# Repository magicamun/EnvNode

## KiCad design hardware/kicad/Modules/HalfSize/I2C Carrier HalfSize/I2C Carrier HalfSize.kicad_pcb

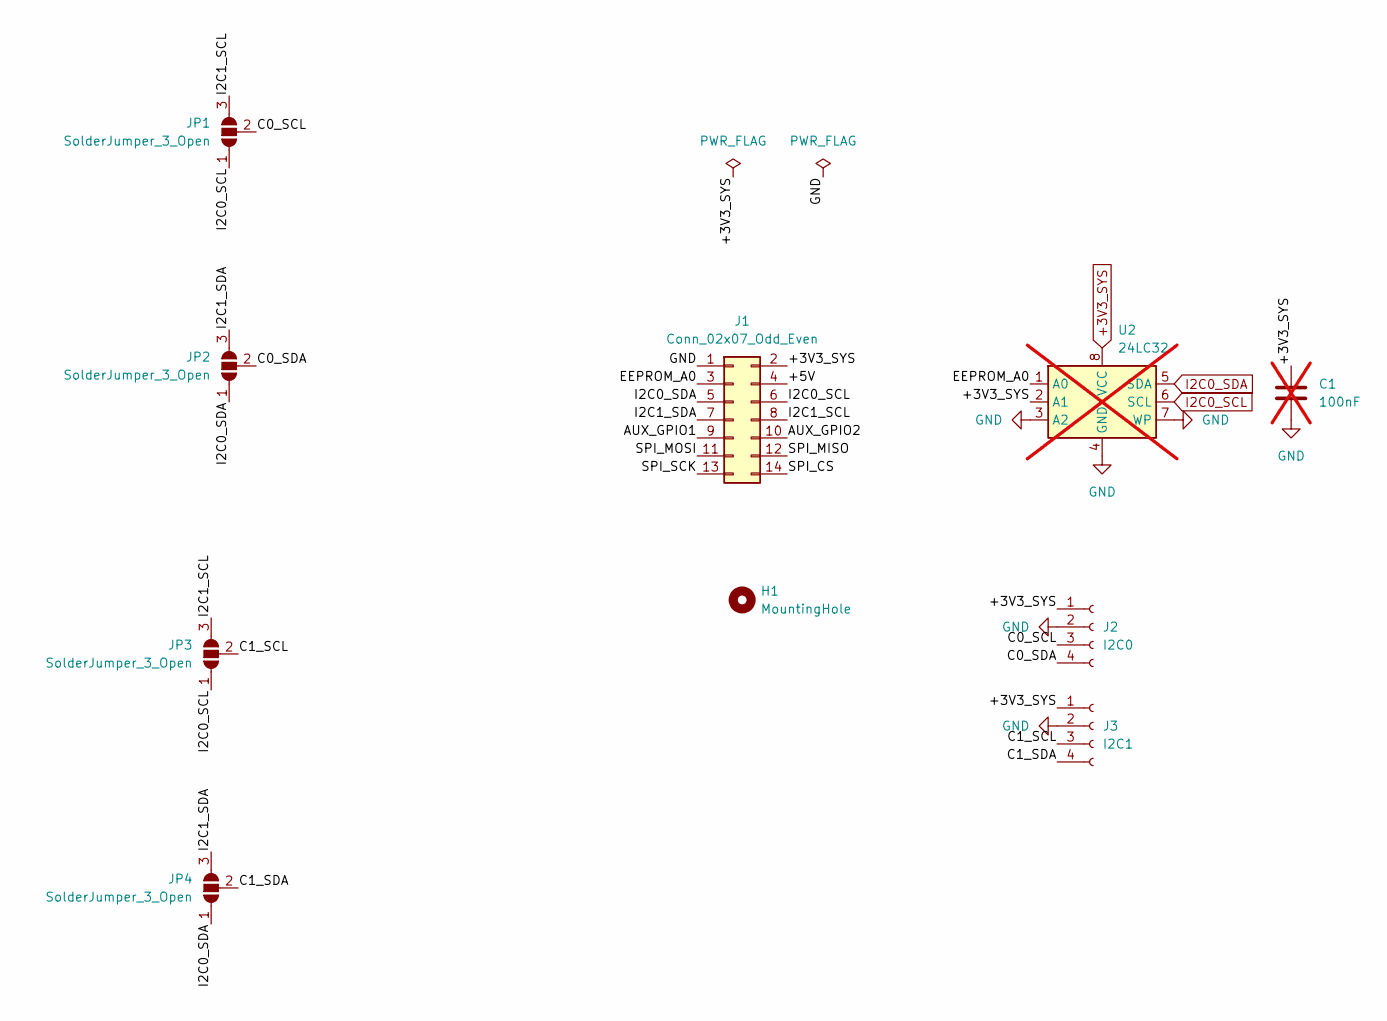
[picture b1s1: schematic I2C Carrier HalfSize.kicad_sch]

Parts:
C1: 100nF; C_1206_3216Metric_Pad1.33x1.80mm_HandSolder; not fitted
H1: MountingHole; MountingHole_2.7mm_M2.5_DIN965
J1: Conn_02x07_Odd_Even; PinHeader_2x07_P2.54mm_Vertical_Bottom
J2: I2C0; PinSocket_1x04_P2.54mm_Vertical
J3: I2C1; PinSocket_1x04_P2.54mm_Vertical
JP1, JP2, JP3, JP4: SolderJumper_3_Open; SolderJumper-3_P1.3mm_Open_RoundedPad1.0x1.5mm
U2: 24LC32; SOIC-8_3.9x4.9mm_P1.27mm; not fitted

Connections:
+3V3_SYS: C1.1, J1.2, J2.1, J3.1, U2.2 (A1), U2.8 (VCC)
/+5V: J1.4
/AUX_GPIO1: J1.9
/AUX_GPIO2: J1.10
/C0_SCL: J2.3, JP1.2 (C)
/C0_SDA: J2.4, JP2.2 (C)
/C1_SCL: J3.3, JP3.2 (C)
/C1_SDA: J3.4, JP4.2 (C)
/EEPROM_A0: J1.3, U2.1 (A0)
/I2C1_SCL: J1.8, JP1.3 (B), JP3.3 (B)
/I2C1_SDA: J1.7, JP2.3 (B), JP4.3 (B)
/SPI_CS: J1.14
/SPI_MISO: J1.12
/SPI_MOSI: J1.11
/SPI_SCK: J1.13
GND: C1.2, J1.1, J2.2, J3.2, U2.3 (A2), U2.4 (GND), U2.7 (WP)
I2C0_SCL: J1.6, JP1.1 (A), JP3.1 (A), U2.6 (SCL)
I2C0_SDA: J1.5, JP2.1 (A), JP4.1 (A), U2.5 (SDA)

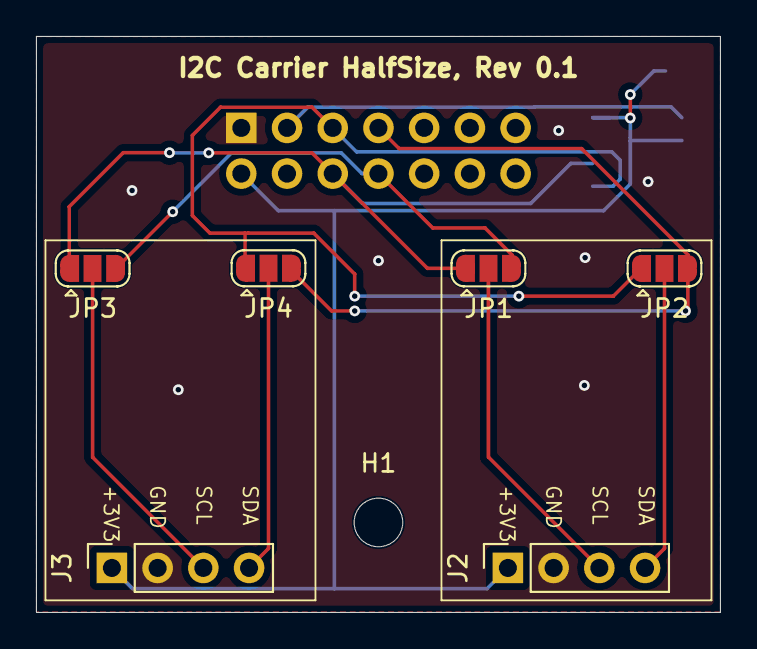
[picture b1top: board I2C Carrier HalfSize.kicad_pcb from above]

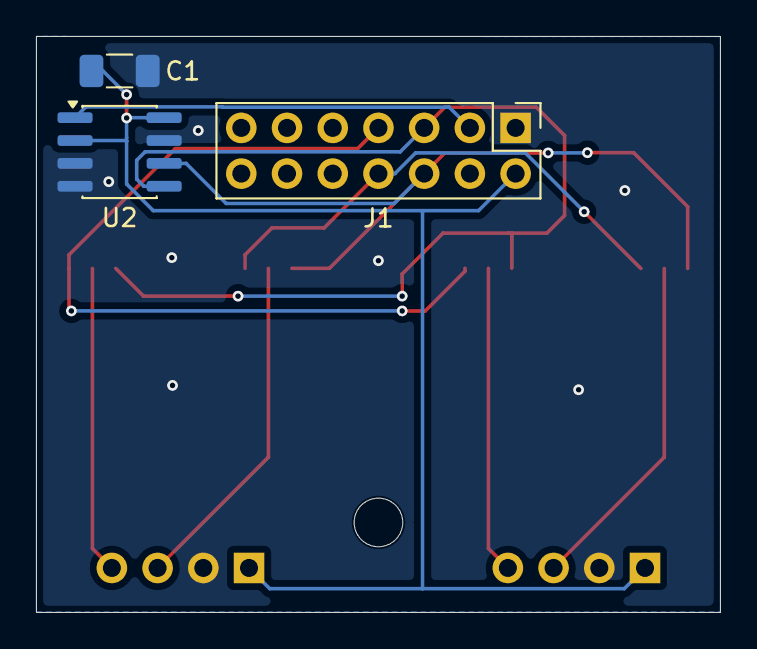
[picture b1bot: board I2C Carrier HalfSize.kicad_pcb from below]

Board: 2 copper layers, 38.0 x 32.0 mm, 10 parts (3 on the bottom side), 11 nets.

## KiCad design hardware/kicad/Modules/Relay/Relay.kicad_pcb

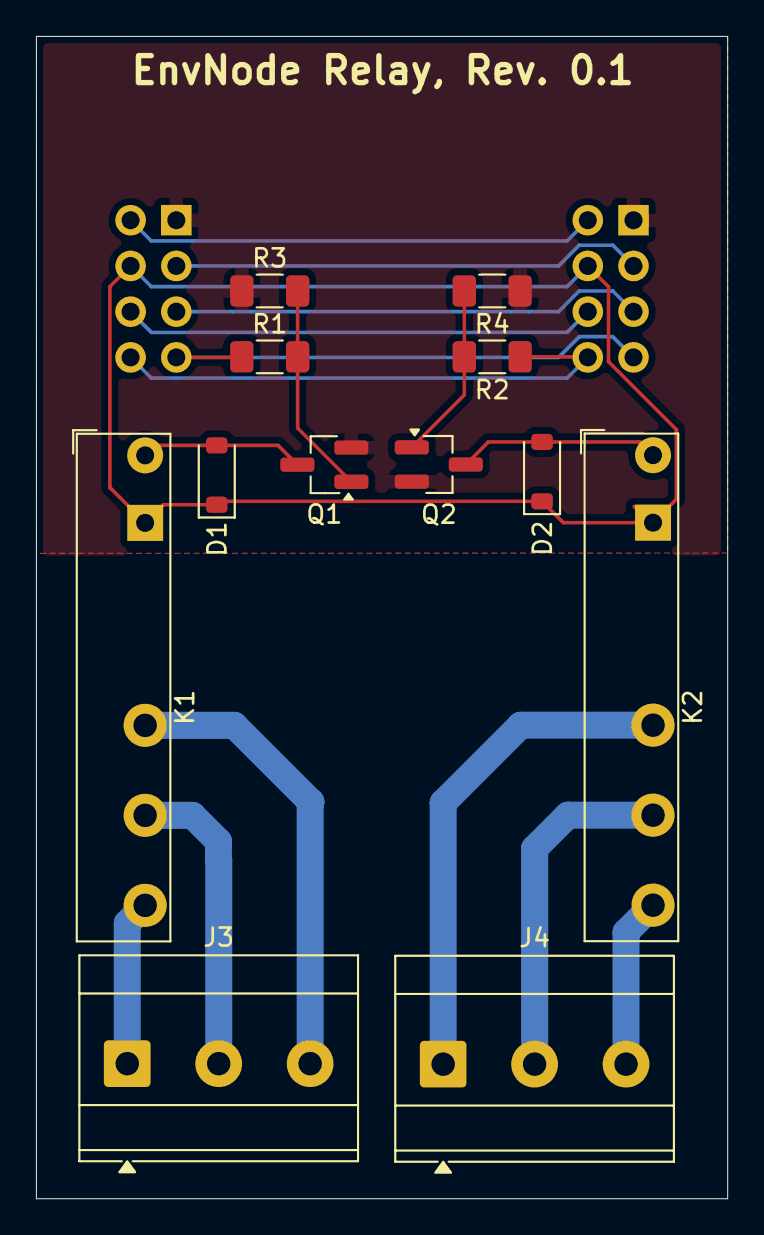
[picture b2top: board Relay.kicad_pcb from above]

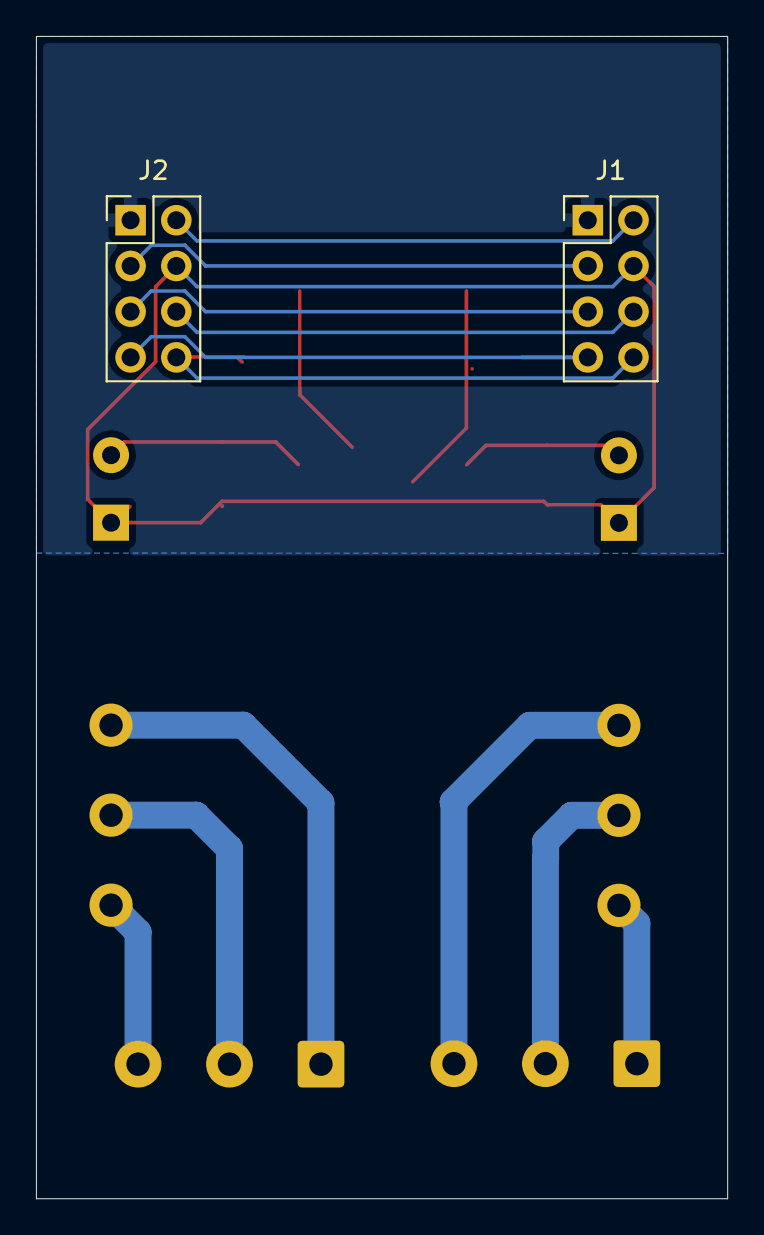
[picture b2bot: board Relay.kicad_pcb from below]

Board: 2 copper layers, 38.4 x 64.6 mm, 14 parts (2 on the bottom side), 18 nets.

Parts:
D1, D2: 1N4148W; D_SOD-123
J1, J2: Conn_02x04_Odd_Even; PinSocket_2x04_P2.54mm_Vertical_Bottom
J3, J4: TerminalBlock_Phoenix_MKDS-3-3-5.08_1x03_P5.08mm_Horizontal
K1, K2: FINDER-34.51; Relay_SPDT_Finder_34.51_Vertical
Q1, Q2: BC817; SOT-23_Handsoldering
R1, R2: 1k; R_1206_3216Metric_Pad1.30x1.75mm_HandSolder
R3, R4: 100k; R_1206_3216Metric_Pad1.30x1.75mm_HandSolder

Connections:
3V3: J1.3, J2.3
5V: D1.1 (K), D2.1 (K), J1.4, J2.4, K1.A1, K2.A1
24V: J1.2, J2.2
/COM1: J3.2, K1.11
/COM2: J4.2, K2.11
/NC1: J3.3, K1.12
/NC2: J4.1, K2.12
/NO1: J3.1, K1.14
/NO2: J4.3, K2.14
GND: J1.1, J2.1, Q1.2 (E), Q2.2 (E), R3.1, R4.1
GPIO1: J1.7, J2.7, R1.1
GPIO2: J1.8, J2.8, R2.1
unnamed: D1.2 (A), K1.A2, Q1.3 (C)
unnamed: D2.2 (A), K2.A2, Q2.3 (C)
unnamed: Q1.1 (B), R1.2, R3.2
unnamed: Q2.1 (B), R2.2, R4.2
SCL: J1.6, J2.6
SDA: J1.5, J2.5

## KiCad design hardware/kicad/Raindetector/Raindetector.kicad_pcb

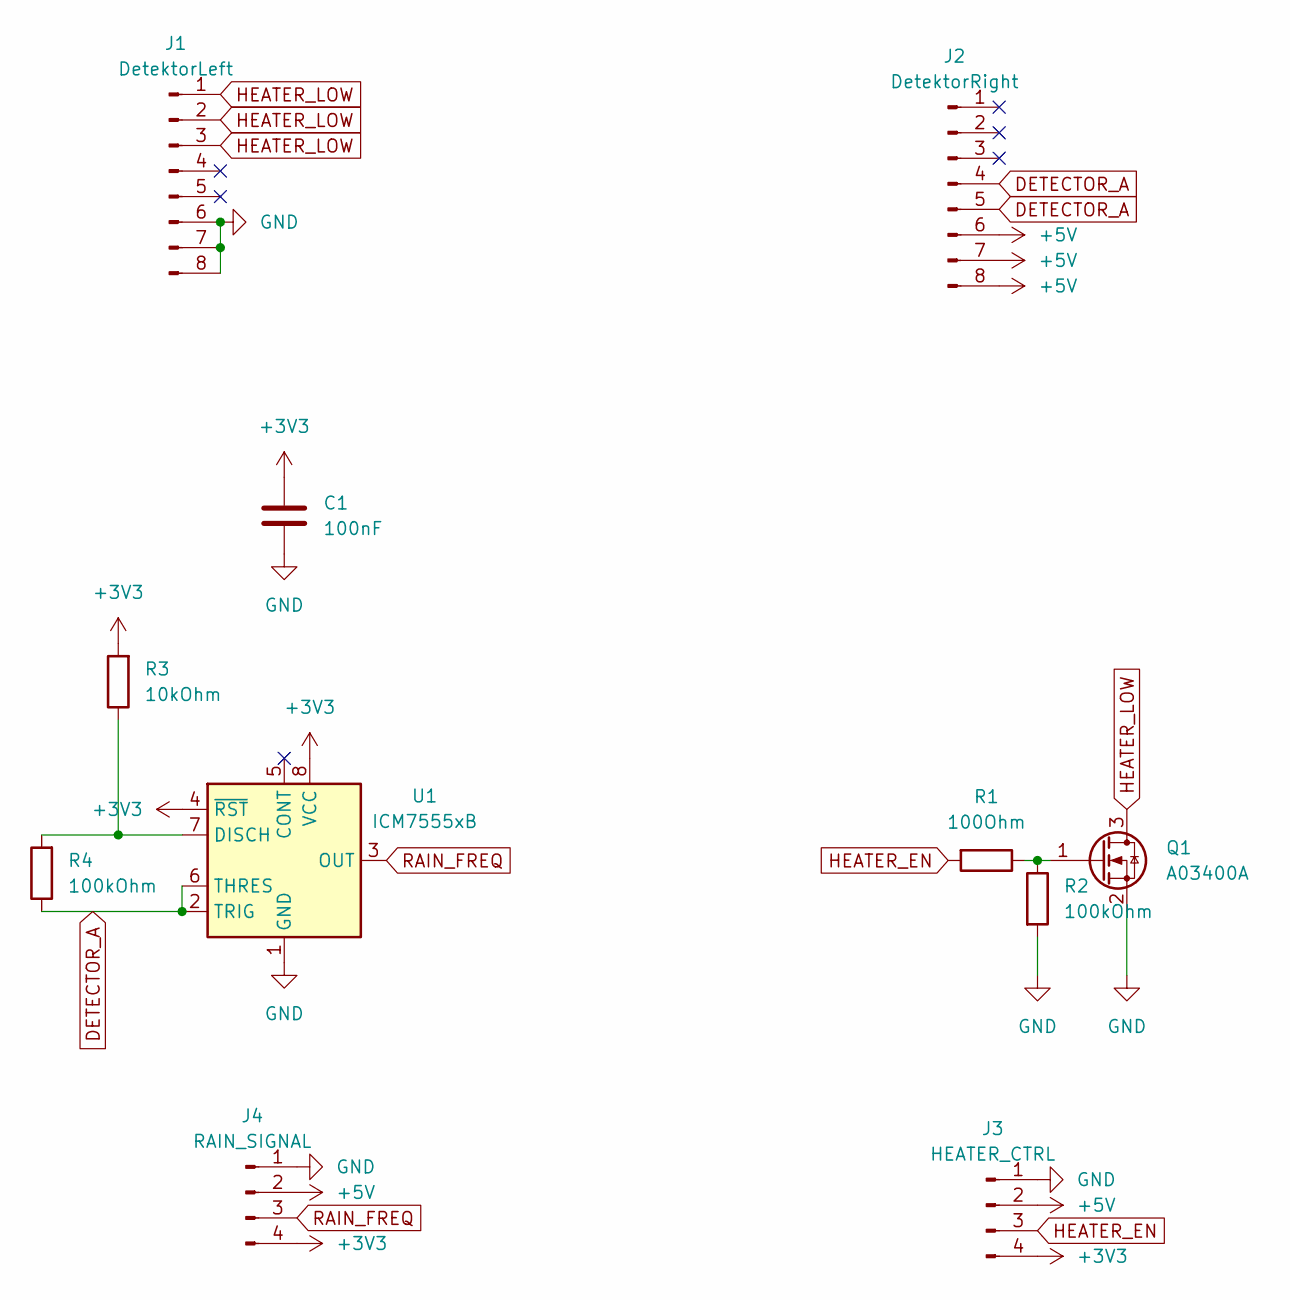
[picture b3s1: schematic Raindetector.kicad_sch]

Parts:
C1: 100nF; C_1206_3216Metric_Pad1.33x1.80mm_HandSolder
J1: DetektorLeft; PinHeader_1x08_P2.54mm_Vertical
J2: DetektorRight; PinHeader_1x08_P2.54mm_Vertical
J3: HEATER_CTRL; PinSocket_1x04_P2.54mm_Vertical
J4: RAIN_SIGNAL; PinSocket_1x04_P2.54mm_Vertical
Q1: A03400A; SOT-23
R1: 100Ohm; R_1206_3216Metric_Pad1.30x1.75mm_HandSolder
R2, R4: 100kOhm; R_1206_3216Metric_Pad1.30x1.75mm_HandSolder
R3: 10kOhm; R_1206_3216Metric_Pad1.30x1.75mm_HandSolder
U1: ICM7555xB; SOIC-8_3.9x4.9mm_P1.27mm

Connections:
+3V3: C1.1, J3.4, J4.4, R3.2, U1.4 (~RST), U1.8 (VCC)
+5V: J2.6, J2.7, J2.8, J3.2, J4.2
DETECTOR_A: J2.4, J2.5, R4.1, U1.2 (TRIG), U1.6 (THRES)
GND: C1.2, J1.6, J1.7, J1.8, J3.1, J4.1, Q1.2 (S), R2.2, U1.1 (GND)
HEATER_EN: J3.3, R1.2
HEATER_LOW: J1.1, J1.2, J1.3, Q1.3 (D)
unnamed: Q1.1 (G), R1.1, R2.1
unnamed: R3.1, R4.2, U1.7 (DISCH)
RAIN_FREQ: J4.3, U1.3 (OUT)

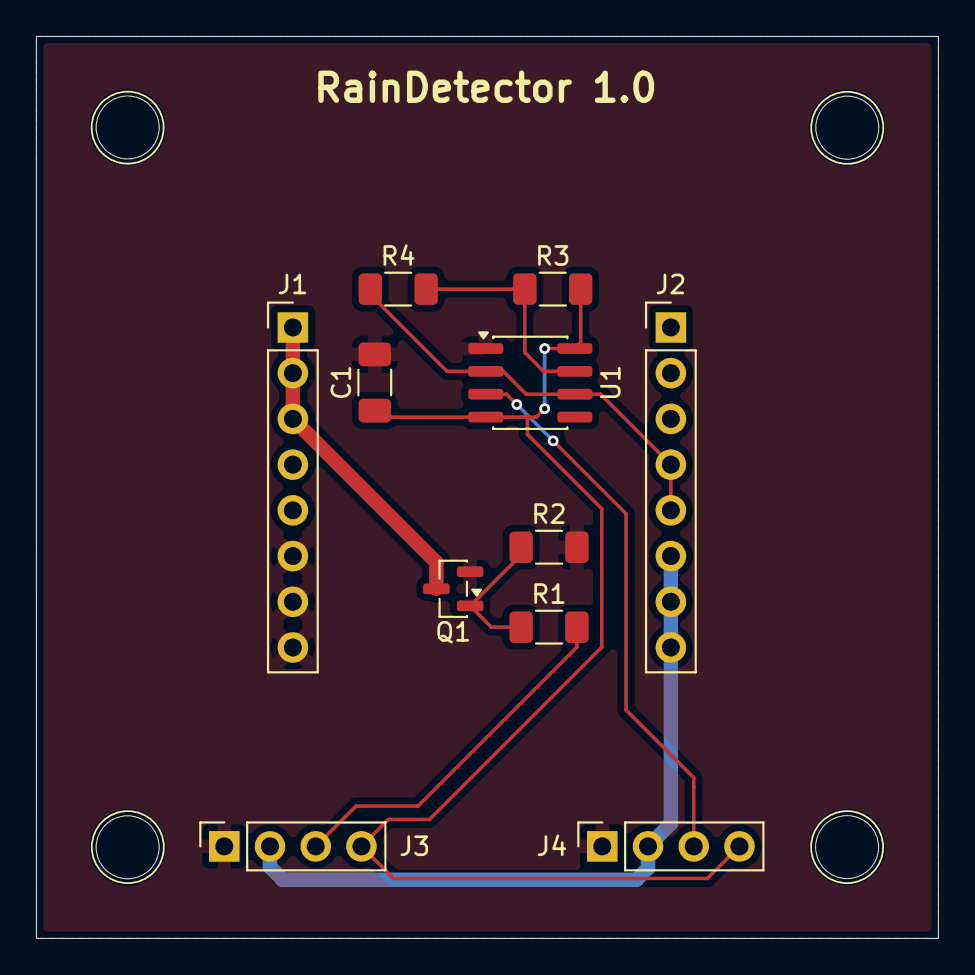
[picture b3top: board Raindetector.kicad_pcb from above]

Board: 2 copper layers, 50.1 x 50.1 mm, 11 parts (0 on the bottom side), 9 nets.

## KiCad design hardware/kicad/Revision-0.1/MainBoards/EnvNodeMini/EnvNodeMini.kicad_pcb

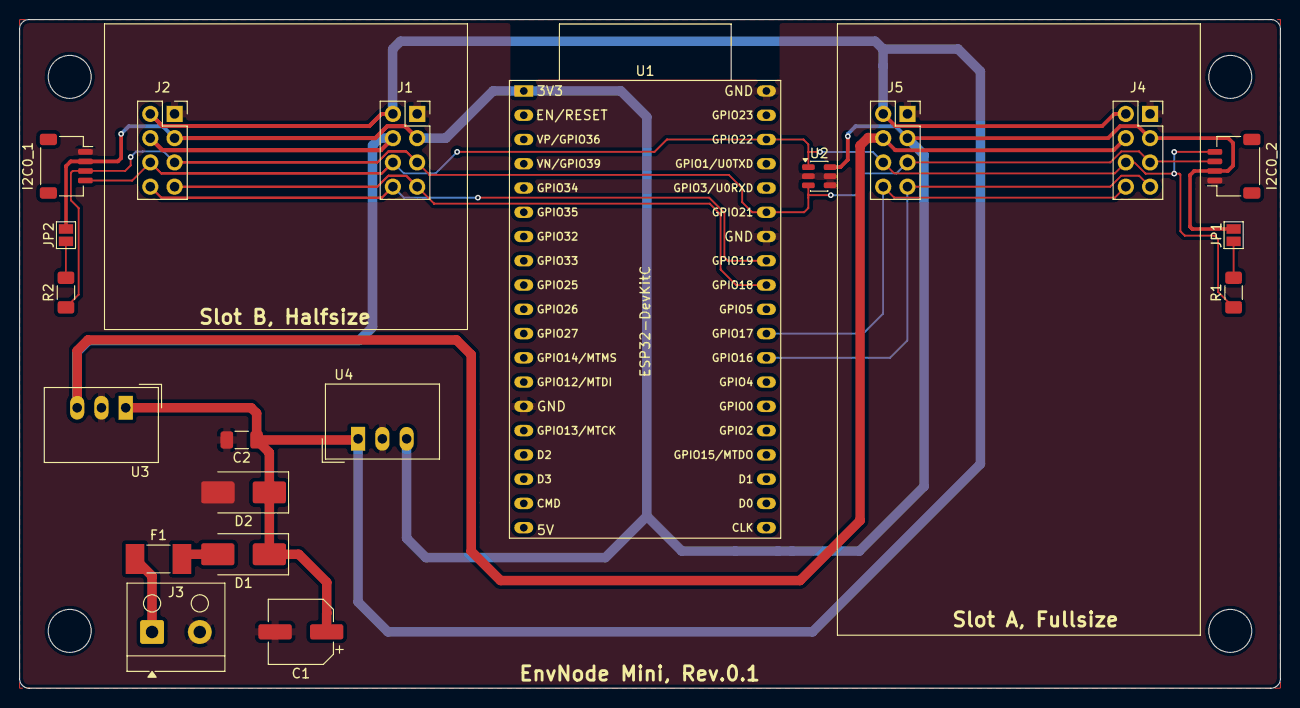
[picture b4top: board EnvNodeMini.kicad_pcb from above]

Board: 2 copper layers, 132.0 x 70.0 mm, 20 parts (0 on the bottom side), 14 nets.

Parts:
C1: 47uF/50V; CP_Elec_6.3x7.7
C2: 100nF / 50V X7R; C_1206_3216Metric_Pad1.33x1.80mm_HandSolder
D1: B360B-13-F; D_SMB_Handsoldering
D2: SMBJ24A; D_SMB_Handsoldering
F1: 2A; Fuse_Littelfuse-NANO2-451_453
I2C0_1, I2C0_2: Conn_01x04_Pin; JST_SH_SM04B-SRSS-TB_1x04-1MP_P1.00mm_Horizontal
J1, J2, J4, J5: Conn_02x04_Odd_Even; PinSocket_2x04_P2.54mm_Vertical
J3: Power; TerminalBlock_RND_205-00001_1x02_P5.00mm_Horizontal
JP1, JP2: Open; SolderJumper-2_P1.3mm_Open_Pad1.0x1.5mm
R1, R2: 4,7 kOhm; R_1206_3216Metric_Pad1.30x1.75mm_HandSolder
U1: ESP32-DevKitC
U2: 24AA025E-OT; SOT-23-6
U3: TSR_1-2450; Converter_DCDC_TRACO_TSR-1_THT
U4: TSR_1-2433; Converter_DCDC_TRACO_TSR-1_THT

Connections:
3V3: I2C0_1.2, I2C0_2.2, J1.3, J2.3, J4.3, J5.3, JP1.2 (B), JP2.2 (B), U1.1 (3V3), U2.6 (V_{CC}), U4.3 (Vout)
5V: J1.4, J2.4, J4.4, J5.4, U3.3 (Vout)
24V: C1.1, C2.1, D1.1 (K), D2.1 (K), J1.2, J2.2, J4.2, J5.2, U3.1 (Vin), U4.1 (Vin)
+24V_IN: F1.1, J3.1
GND: C1.2, C2.2, D2.2 (A), I2C0_1.1, I2C0_2.1, J1.1, J2.1, J3.2, J4.1, J5.1, U1.14 (GND), U1.32 (GND), U1.38 (GND), U2.2 (V_{SS}), U2.4 (A1), U2.5 (A0), U3.2 (GND), U4.2 (GND)
GPIO16: J4.7, J5.7, U1.27 (GPIO16)
GPIO17: J4.8, J5.8, U1.28 (GPIO17)
GPIO18: J1.7, J2.7, U1.30 (GPIO18)
GPIO19: J1.8, J2.8, U1.31 (GPIO19)
I2C0_SCL: I2C0_1.4, I2C0_2.4, J1.6, J2.6, J4.6, J5.6, R1.1, U1.36 (GPIO22), U2.1 (SCL)
I2C0_SDA: I2C0_1.3, I2C0_2.3, J1.5, J2.5, J4.5, J5.5, R2.1, U1.33 (GPIO21), U2.3 (SDA)
unnamed: D1.2 (A), F1.2
unnamed: JP1.1 (A), R1.2
unnamed: JP2.1 (A), R2.2

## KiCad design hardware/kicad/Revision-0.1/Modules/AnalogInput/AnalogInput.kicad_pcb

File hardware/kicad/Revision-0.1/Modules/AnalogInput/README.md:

# EnvNode AnalogInput HalfSize

## Purpose

`AnalogInput` is a HalfSize EnvNode daughterboard for one 4–20 mA current-loop pressure probe. It supplies the probe from the module's `24V` rail, converts the loop current into a voltage across a precision 150 ohm burden resistor, filters and clamps the measurement signal, and digitizes it with an ADS1115 on the system I2C bus.

The module is derived from `EmptyModule_HalfSize` and uses the standardized daughterboard interface design block.

## Project Files

- `AnalogInput.kicad_pro`
- `AnalogInput.kicad_sch`
- `AnalogInput.kicad_pcb`

## Module Interface

J1 and J2 are bottom-mounted module receptacles using:

`EnvNode-Footprints:PinSocket_2x04_P2.54mm_Vertical_Bottom`

| Pin | Net | AnalogInput use |
| ---: | --- | --- |
| 1 | `GND` | Circuit reference and current-return reference |
| 2 | `24V` | Supplies the external current-loop probe through J3 |
| 3 | `3V3` | Supplies U1 and the input-clamp rail |
| 4 | `5V` | Passed through between J1 and J2; unused by the measurement circuit |
| 5 | `SDA` | ADS1115 I2C data |
| 6 | `SCL` | ADS1115 I2C clock |
| 7 | `GPIO1` | Passed through between J1 and J2; unused by the measurement circuit |
| 8 | `GPIO2` | Passed through between J1 and J2; unused by the measurement circuit |

The completed module does not source any shared power rail. The mainboard remains responsible for rail generation, protection, and power budgeting.

## Probe Connection and Signal Path

J3 is the two-wire probe connector:

| J3 pin | Net | Function |
| ---: | --- | --- |
| 1 | `24V` | Probe supply |
| 2 | `LOOP_RETURN` | Probe current return and measurement input |

The intended probe is polarity independent. Other 4–20 mA transmitters may be polarity sensitive and must be checked before connection.

The measurement path is:

1. The probe current returns through `LOOP_RETURN`.
2. R1, 150 ohm, converts 4–20 mA into approximately 0.6–3.0 V.
3. R2, 4.7 kohm, and C1, 1 uF, form a low-pass filter with a nominal cutoff of approximately 34 Hz.
4. D1, BAT54S, clamps the ADC input toward GND and 3V3.
5. U1, ADS1115IDGS, measures the filtered signal on AIN0.

At 20 mA, R1 dissipates approximately 60 mW. The specified part is 150 ohm, 0.1 %, no more than 25 ppm/K, and rated above 0.125 W. Changing R1 changes the measurement range and requires corresponding firmware calibration and input-range review.

C2, 100 nF, is the local ADS1115 supply decoupling capacitor between 3V3 and GND.

AIN1, AIN2, AIN3, and `ALERT/RDY` are intentionally not connected.

## I2C Address Selection

The ADS1115 address is selected by closing exactly one solder jumper:

| Jumper | ADDR connection | I2C address |
| --- | --- | --- |
| JP1 | GND | `0x48` |
| JP2 | 3V3 | `0x49` |
| JP3 | SDA | `0x4A` |
| JP4 | SCL | `0x4B` |

All four jumpers are open in the PCB design. **Exactly one jumper must be solder-closed before the module is powered.** Leaving all jumpers open leaves the ADDR input undefined. Closing more than one jumper can short system nets together and must not be done.

The PCB silkscreen states `ADDR: Close exactly One` and labels all four address choices.

## Firmware Requirements

The firmware must:

- use the EnvNode system I2C bus;
- use the address selected by JP1–JP4;
- configure ADS1115 AIN0 as the measurement input;
- configure a full-scale range of at least plus/minus 4.096 V; and
- convert the measured burden voltage to loop current using the actual calibrated R1 value.

The ADS1115 power-up default range of plus/minus 2.048 V is not suitable for the complete 4–20 mA range with a 150 ohm burden resistor. It would clip above approximately 13.7 mA.

The nominal conversion is:

```text
loop_current_A = measured_voltage_V / 150 ohm
```

Pressure conversion depends on the connected probe's specified pressure range and transfer characteristic and is therefore not fixed by this module.

## Bring-up Checklist

1. Inspect U1 and D1 orientation and all solder joints.
2. Verify that exactly one of JP1–JP4 is closed and confirm the resulting I2C address.
3. Verify R1 is the specified precision 150 ohm part.
4. Power the module from current-limited SELV supplies without the probe connected.
5. Confirm 3V3 at U1 and verify the ADS1115 is detected at the selected address.
6. Configure the ADS1115 for at least the plus/minus 4.096 V range.
7. Apply a known loop current or current-loop simulator at J3.
8. Verify approximately 0.6 V at 4 mA, 1.8 V at 12 mA, and 3.0 V at 20 mA.
9. Verify the reported current and pressure conversion across the intended operating range.
10. Refill zones and rerun ERC and DRC before release.

## Manufacturing and Assembly Status

The production BOM and assembly documentation are not yet released. Component manufacturer part numbers, procurement alternatives, assembly drawings, polarity and orientation views, and inspection criteria must be completed and reviewed before assembling a production batch.

## Validated Design State

The design was checked on 2026-08-26 with KiCad 10:

- schematic ERC: no errors or warnings;
- PCB DRC: no violations;
- no unconnected pads or footprint errors;
- no global schematic labels;
- ADS1115 supply decoupling present;
- four intentionally open and correctly labeled address-selection jumpers;
- one linked daughterboard-interface design-block group;
- no routing vias; and
- successful top-side and bottom-side 3D construction and visual review.

This validation covers schematic consistency and the encoded two-dimensional PCB rules. Final performance requires physical bring-up, probe calibration, power-supply verification, and EMC assessment in the complete EnvNode assembly.

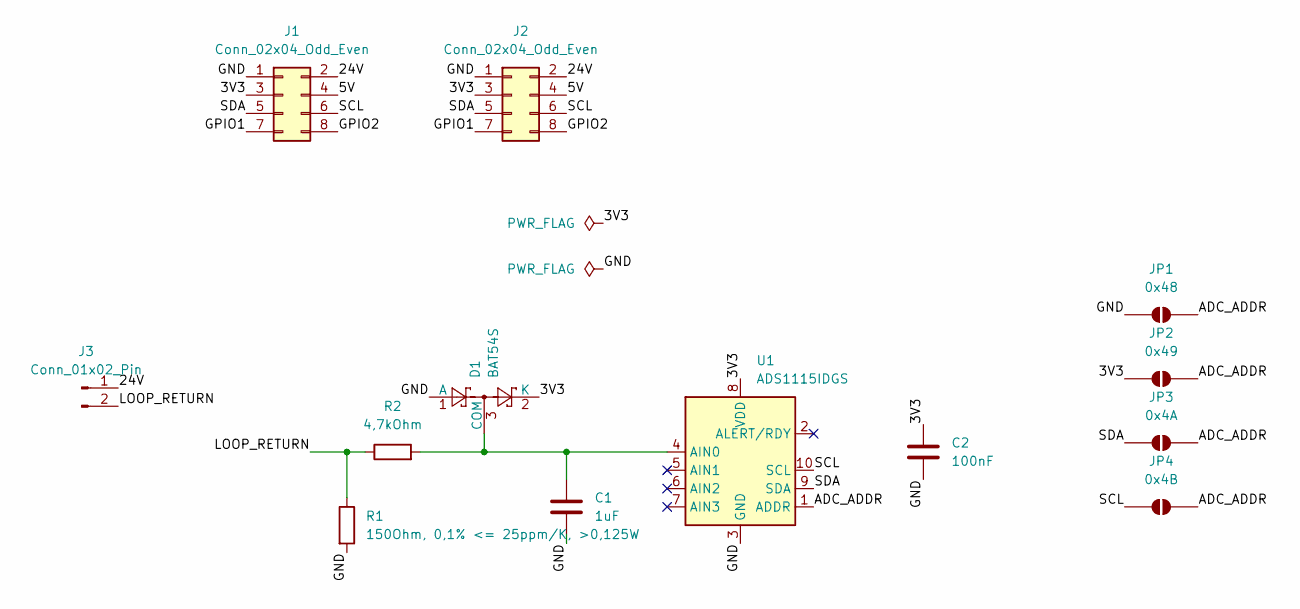
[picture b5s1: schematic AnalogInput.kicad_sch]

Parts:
C1: 1uF; C_1206_3216Metric_Pad1.33x1.80mm_HandSolder
C2: 100nF; C_1206_3216Metric_Pad1.33x1.80mm_HandSolder
D1: BAT54S; SOT-23
J1, J2: Conn_02x04_Odd_Even; PinSocket_2x04_P2.54mm_Vertical_Bottom
J3: Conn_01x02_Pin; PinSocket_1x02_P2.54mm_Vertical
JP1: 0x48; SolderJumper-2_P1.3mm_Open_Pad1.0x1.5mm
JP2: 0x49; SolderJumper-2_P1.3mm_Open_Pad1.0x1.5mm
JP3: 0x4A; SolderJumper-2_P1.3mm_Open_Pad1.0x1.5mm
JP4: 0x4B; SolderJumper-2_P1.3mm_Open_Pad1.0x1.5mm
R1: 150Ohm, 0,1% <= 25ppm/K, >0,125W; R_Axial_DIN0207_L6.3mm_D2.5mm_P7.62mm_Horizontal
R2: 4,7kOhm; R_1206_3216Metric_Pad1.30x1.75mm_HandSolder
U1: ADS1115IDGS; TSSOP-10_3x3mm_P0.5mm

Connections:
/3V3: C2.1, D1.2 (K), J1.3, J2.3, JP2.1 (A), U1.8 (VDD)
/5V: J1.4, J2.4
/24V: J1.2, J2.2, J3.1
/ADC_ADDR: JP1.2 (B), JP2.2 (B), JP3.2 (B), JP4.2 (B), U1.1 (ADDR)
/GND: C1.2, C2.2, D1.1 (A), J1.1, J2.1, JP1.1 (A), R1.2, U1.3 (GND)
/GPIO1: J1.7, J2.7
/GPIO2: J1.8, J2.8
/LOOP_RETURN: J3.2, R1.1, R2.1
/SCL: J1.6, J2.6, JP4.1 (A), U1.10 (SCL)
/SDA: J1.5, J2.5, JP3.1 (A), U1.9 (SDA)
unnamed: C1.1, D1.3 (COM), R2.2, U1.4 (AIN0)

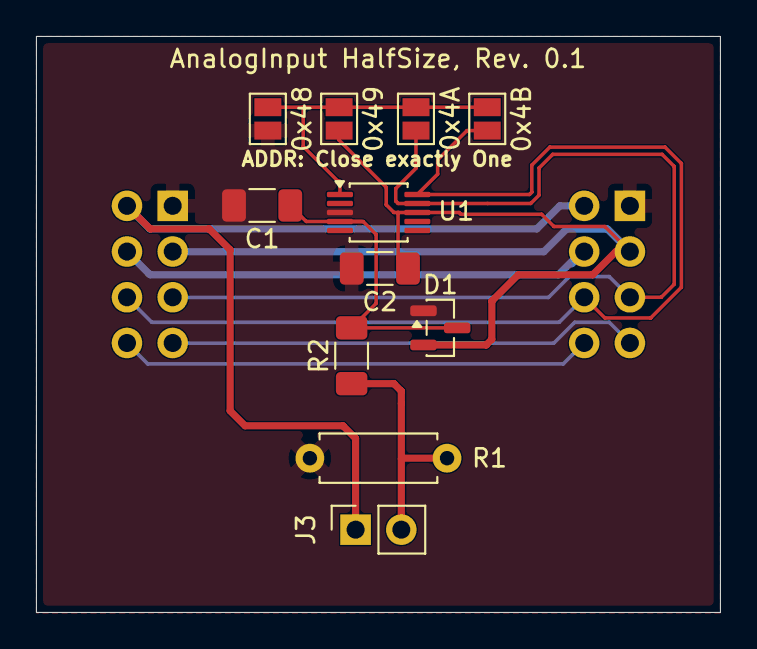
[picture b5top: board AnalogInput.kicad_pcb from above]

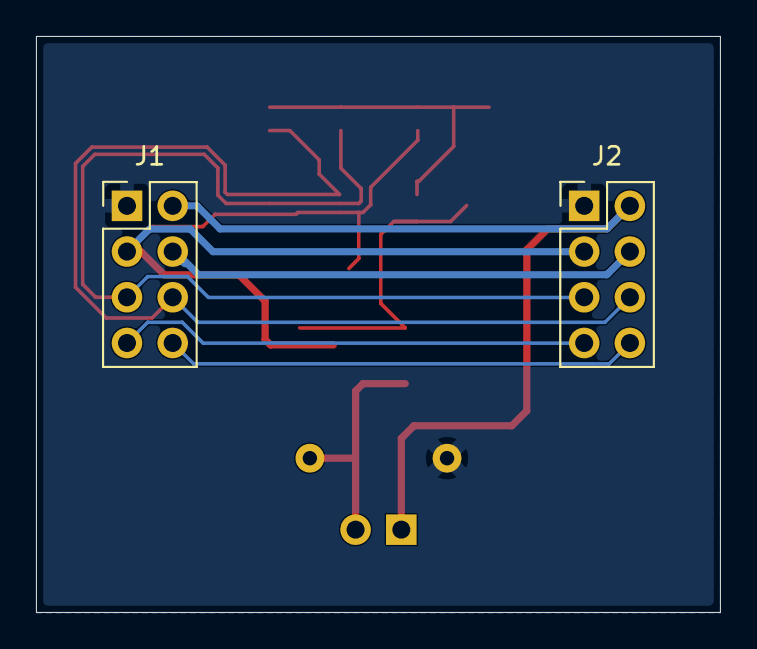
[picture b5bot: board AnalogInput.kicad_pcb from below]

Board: 2 copper layers, 38.0 x 32.0 mm, 13 parts (2 on the bottom side), 11 nets.
